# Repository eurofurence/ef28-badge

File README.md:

# Eurofurence 28 Cyber Badge

The cyber LED-Badge is a unique piece of wearable tech. At its core is a rigid
PCB (printed circuit board), assembled with electronic components, carefully
designed to be both functional and visually striking. On the back, you’ll find
a battery pack that powers the badge, ensuring that it can light up in a
spectrum of vibrant colors throughout the event.

The badge features 17 RGB LEDs, which can be controlled to display different
colors and patterns, allowing you to customize your experience. Whether you
want to flash your favorite colors, sync up with others, or simply let your
badge pulse with light as you move through the convention, the choice is yours.

## Technical Details

You can find the full schematics and PCB files in the
[Hardware Details](#hardware-details) section.

- Height: 15.9 cm
- Width: 7.7 cm
- Weight (w/o batteries): 56 g
- Weight (with batteries): ~126 g
- LEDs: 17x WS2812B RGB LEDs
- CPU: ESP32-S3-WROOM-1-N16R8 (Dual-Core, 16MB of Flash, Bluetooth, Wi-Fi)
- Battery holder: 3x AA batteries
- Runtime: Depending on the operation mode and used features, several to many hours
- Unpopulated headers: 2x8 GPIO, SAO 1.69
- User input: 2 touch buttons
- Attachment: Dual-nylon-loop lanyard (included)
- Connectivity: USB-C connector for powering or programming
- Power: Mechanical power switch

# Usage and features

See this page: [How to use your badge](https://www.eurofurence.org/EF28/badge/manual)

## Serial Output / Logging

The badge logs most of its actions and current state onto the serial USB
console. It is available after connecting the badge via USB to your computer
and uses 115200 Baud 8N1.

To read the serial output you can use the serial monitor of your choice, for
example, the integrated serial monitor within VS Code (`CTRL + ALT + S`):

You can also use your favorite serial monitor, for example [minicom](https://salsa.debian.org/minicom-team/minicom):
`minicom -D /dev/ttyACM0 -b 115200`

## Note on LED brightness

You can configure the brightness of your badge, see the manual [How to use your badge](https://www.eurofurence.org/EF28/badge/manual). If you modify your firmware, do not push the LEDs too hard. We limited the brightness on purpose to around 45 of 255 since the 5V boot converter cannot handle more. If you use just one color channel, values up to 100/255 might work. But they are plenty bright at 45 of 255. Higher values cause the 5V rail to break down and the LEDs start flickering badly.

# Building Your Own Firmware

The badge firmware is built using [PlatformIO](https://platformio.org/), an
extension for [Visual Studio Code](https://code.visualstudio.com/) that allows
beginners to quickly get hacking.

### Building with Visual Studio Code (VCS)

To set up your development environment, you need to:

1. Install Visual Studio Code and PlatformIO, as described in the official
   [PlatformIO documentation](https://docs.platformio.org/en/latest/integration/ide/vscode.html#installation)
2. Clone this repository to a suitable location (here: `~/git/ef28-badge`)
3. Open the project under `~/git/ef28-badge` using the PlatformIO IDE
4. Copy `include/secrets.h.dist` to `include/secrets.h` and adjust as needed
5. Execute the build by pressing the build button (1) or using the hotkey (`CTRL + ALT + B`)
6. Check that your build was successful (2)

_Note: The first build can take a while since additional tools and libraries
may need to be downloaded_

### Building from CLI

You can archive most things with the `pio` command from PlatformIO.

* Build firmware: `pio run`
* Upload firmware: `pio run --target upload`
* Clean generated files: `pio run --target clean`
* Attach serial monitor: `pio device monitor`

## Component Overview

The core of this firmware is implemented as a tick-based finite state machine
(FSM). Each operation mode is reflected by a corresponding FSM state.
Interrupts, e.g., from touch zones, trigger events which will be processed by
the FSM in the order they occurred during each tick. Every FSM state can define
its own tick rate. Board features, such as LEDs and touch zones, are available
via easy to use high-level APIs (see `lib/`).

A quick overview of the firmware components:

- `main.cpp`: The main entry point for the firmware. Initializes everything and
  ignites the FSM.
- `include/`: C++ headers
- `include/secrets.h(.dist)`: Custom defines for Wi-Fi and OTA
- `lib/EFBoard/`: Low-level initialization and power management
- `lib/EFLed/`: High-level interface to board LEDs, uses
  [FastLED](https://fastled.io/) under the hood
- `lib/EFLogging/`: Basic serial logging facilities
- `lib/EFTouch/`: High-level interface to touch sensors
- `src/FSM.cpp`: Implementation of the FSM logic
- `src/states/`: Implementation of all FSM states

## Flashing

After you've built your firmware, you can flash it by either connecting the
badge via USB to your computer, or by using over-the-air (OTA) updates.

_Note: OTA updates are only supported after an initial flash using a USB
connection_

### USB

To flash the firmware via USB, you need to:

1. Have a successful build of your firmware
2. Connect the badge via USB to your computer
3. **Close all serial monitors** that use the badges USB device
4. Click the upload button (1) or use the hotkey (`CTRL + ALT + U`)
5. Wait for the flashing to finish (2). Your badge will reboot after flashing.

_Note: Linux users might need to install the
[PlatformIO udev rules](https://docs.platformio.org/en/stable//core/installation/udev-rules.html)
prior to the first flashing._

#### Notes and Pitfalls

If you encounter issues flashing via USB, try the following:

* Some USB cables or ports are flaky. Try a different USB port or change the
  USB-C -> USB-C cable to a USB-A -> USB-C or vice versa.
* Make sure no program is opening the serial port while you flash. For example
  serial monitors in auto-connect mode.
* If it still fails, bridge the boot-pins when turning on. The badge should
  load into a simple bootloader and wait.

### Over-the-Air Updates (OTA)

If you want to flash the badge using over-the-air updates (OTA), it must be
connected to the same Wi-Fi network as your computer.

To flash a badge using OTA, you need to:

1. Make sure to have the correct Wi-Fi credentials supplied in `include/secrets.h`
2. Determine the badge IP address
    - This can be done by connecting your badge to your computer, opening the
      serial monitor, and letting it connect to your Wi-Fi. After a successful
      connection, the badge will print its IP and MAC addresses to the serial console.
3. Uncomment all `upload_*` entries in your `platformio.ini` and adjust
   `upload_port` to the IP address of your badge.
4. Ensure that the badge is in OTA mode
5. Click the upload button or use the hotkey (`CTRL + ALT + U`)
6. Wait for the flashing to finish. The badge will display the OTA progress
   using the LED bar, and the dragon eye will flash three times after a
   successful OTA update.

# Hardware Details

All hardware details, schematics, and PCB files of the badge are released as
[Open Source Hardware](https://www.oshwa.org/). Feel free to share, use, remix,
and extend them to your likings.

You can find the full [KiCad](https://www.kicad.org/) files inside the
`hardware` directory.

For convenience, here is an exported PDF version of the schematics:

# Releases

The release-versions are based on [CalVer](https://calver.org/), with the pattern `vYYYY.MM.DD(-SUB)` where `SUB` is for potential sub-daily releases.

# Useful links

* ESP32-S3 Pin-out and functions: https://github.com/atomic14/esp32-s3-pinouts

# Credits

This badge was designed, crafted and programmed with much love and dedication
by: [DarkRat](https://github.com/dunkelratte), [Token](https://github.com/TokenRat),
[Irah](https://github.com/tridekdu), [Honigeintopf](https://github.com/ngandrass).

The wonderful artwork is done by [Fleeks](https://www.furaffinity.net/user/fleeks).

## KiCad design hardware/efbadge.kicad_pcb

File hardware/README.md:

# Hardware

This is a [KiCad](https://www.kicad.org/) project.

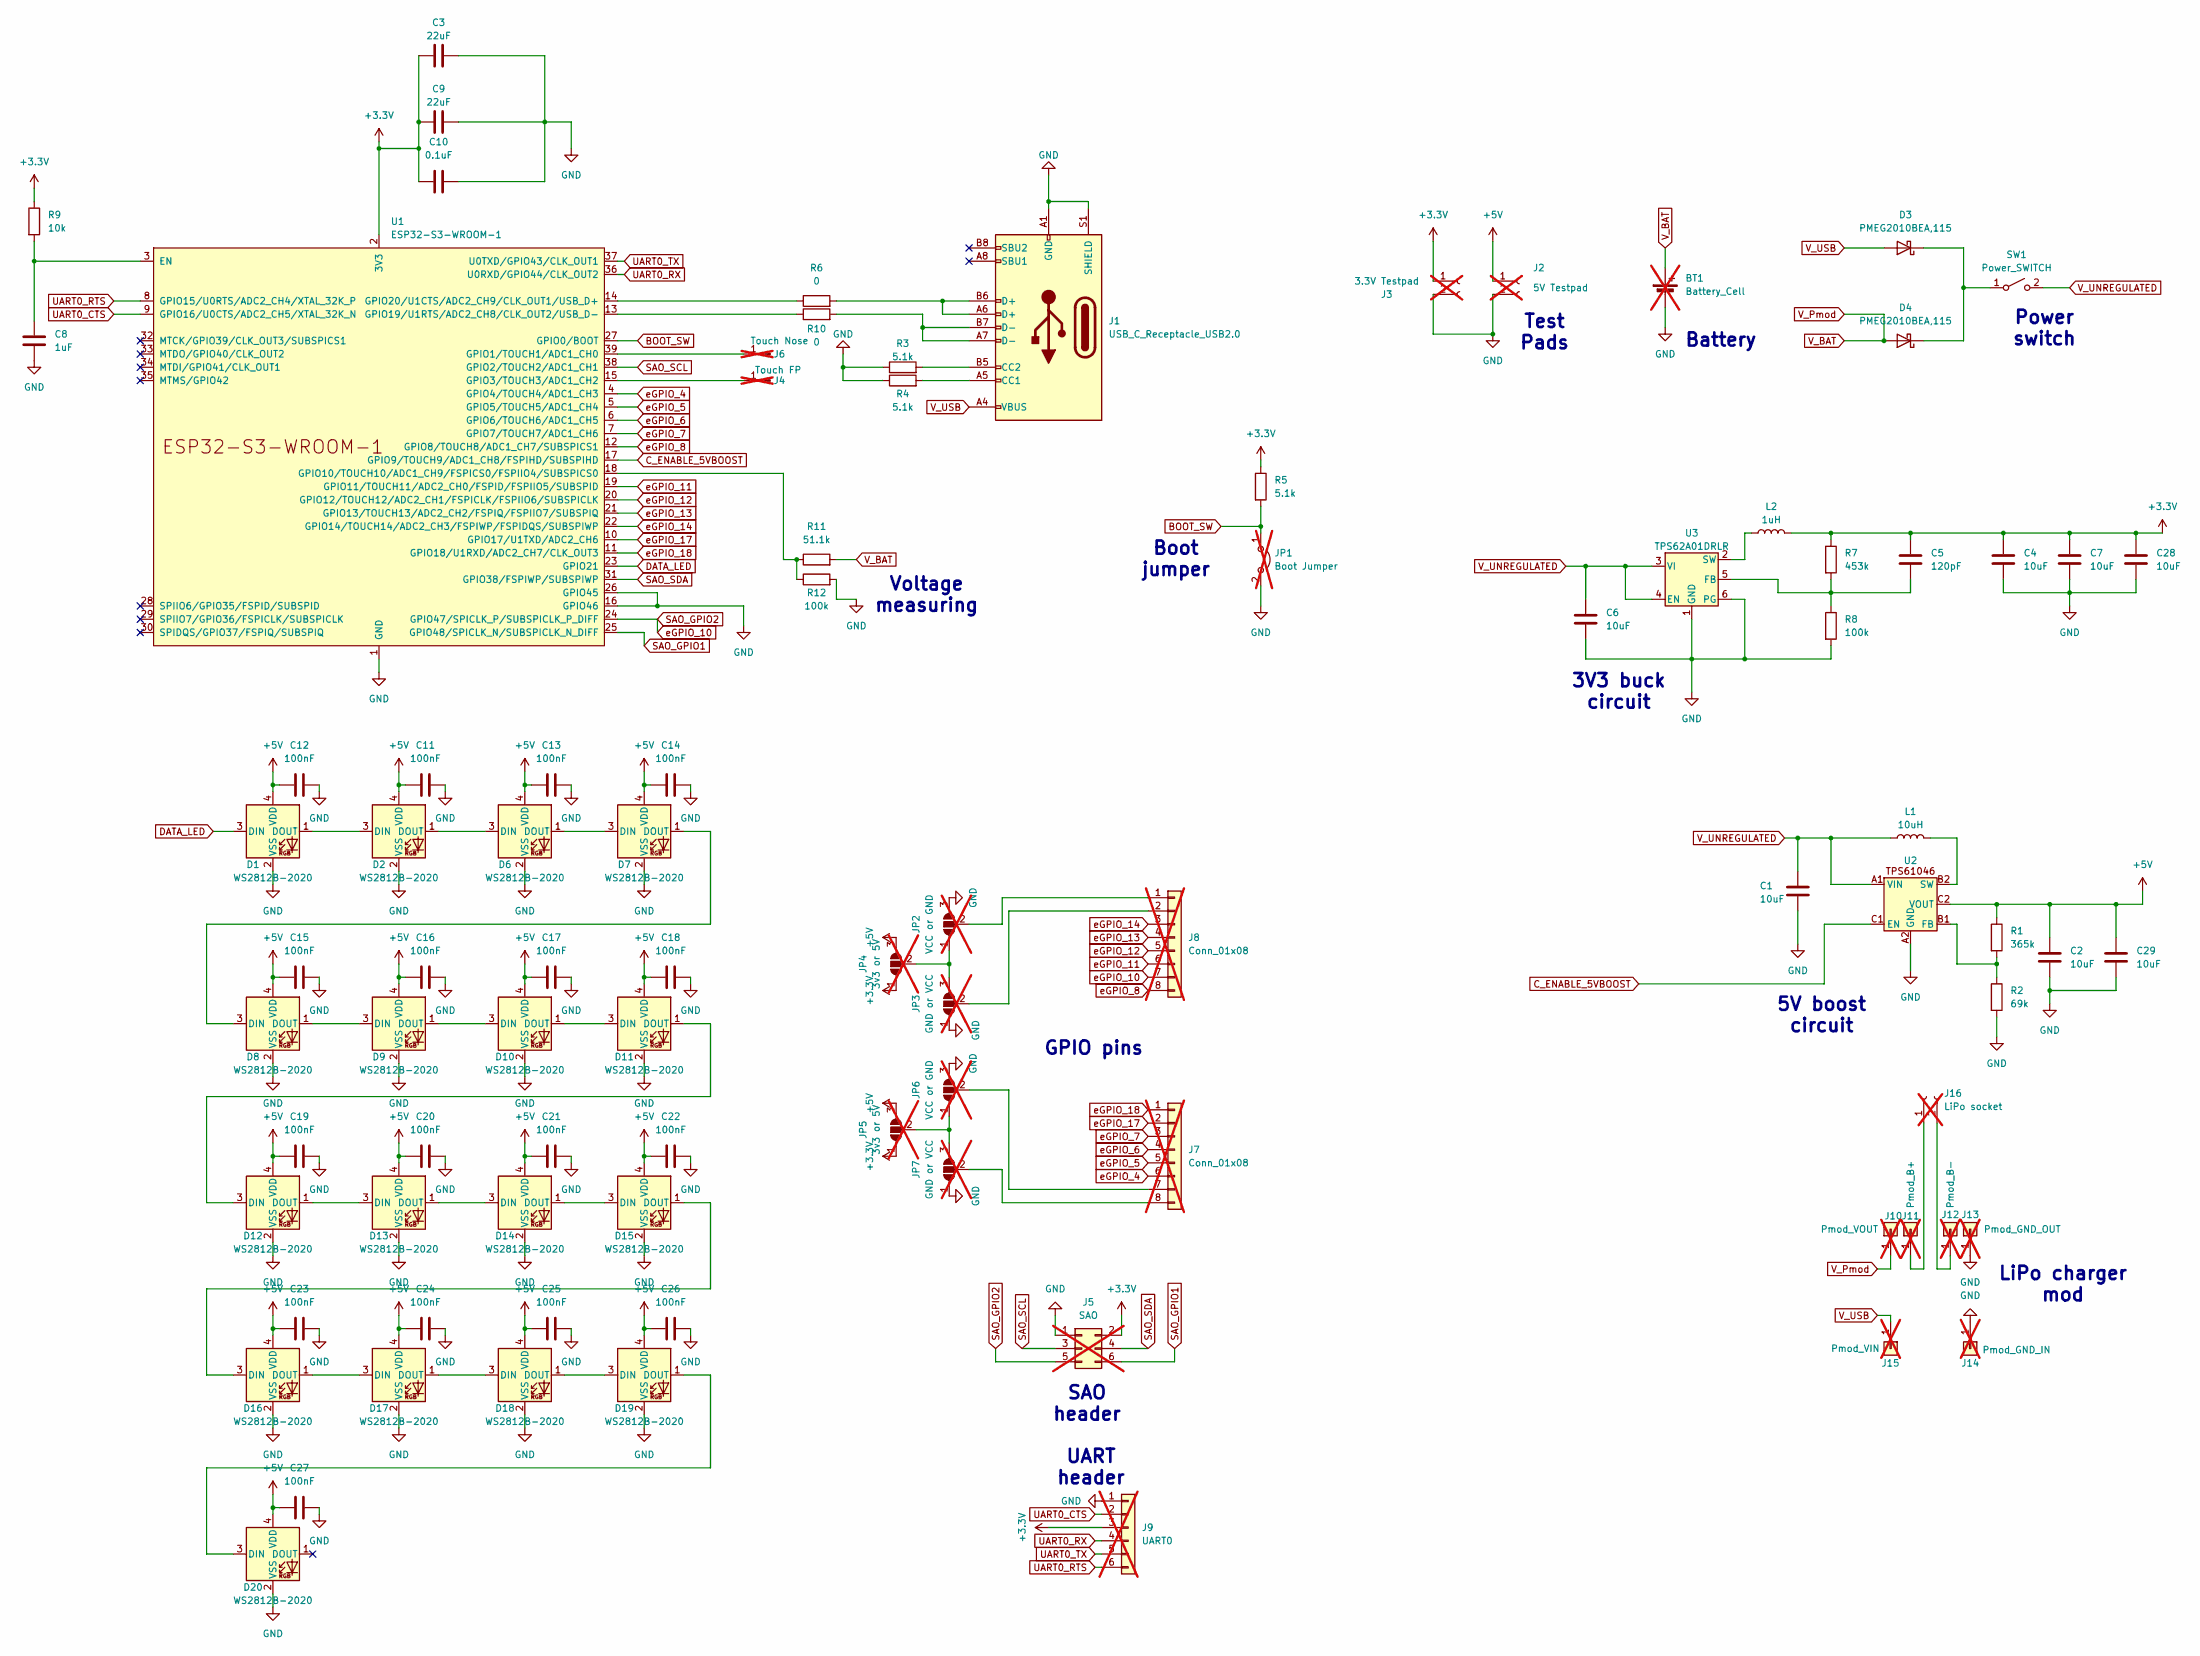
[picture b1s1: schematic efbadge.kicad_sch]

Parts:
BT1: Battery_Cell; BatteryHolder_TruPower_BH-331P_3xAA; Digikey 36-2464-ND; not fitted
C1, C2, C4, C6, C7, C28, C29: 10uF; C_0603_1608Metric; LCSC C182375
C3, C9: 22uF; C_0603_1608Metric; LCSC C15500
C5: 120pF; C_0603_1608Metric; LCSC C61636
C8: 1uF; C_0603_1608Metric; LCSC C309479
C10: 0.1uF; C_0603_1608Metric; LCSC C2846678
C11, C12, C13, C14, C15, C16, C17, C18, C19, C20, C21, C22, C23, C24, C25, C26, C27: 100nF; C_0603_1608Metric_Pad1.08x0.95mm_HandSolder; LCSC C14663
D1, D2, D6, D7, D8, D9, D10, D11, D12, D13, D14, D15, D16, D17, D18, D19, D20: WS2812B-2020; LED_WS2812B-2020_PLCC4_2.0x2.0mm; LCSC C965555
D3, D4: PMEG2010BEA,115; D_SOD-323; LCSC C455041
J1: USB_C_Receptacle_USB2.0; USB_C_Receptacle_G-Switch_GT-USB-7010ASV; LCSC C165948
J2: 5V Testpad; PinHeader_1x02_P2.54mm_Vertical; not fitted
J3: 3.3V Testpad; PinHeader_1x02_P2.54mm_Vertical; not fitted
J4: Touch FP; Badge_Touch; not fitted
J5: SAO; PinHeader_2x03_P2.54mm_Vertical; not fitted
J6: Touch Nose; Badge_Touch; not fitted
J7, J8: Conn_01x08; PinHeader_1x08_P2.54mm_Horizontal; not fitted
J9: UART0; PinHeader_1x06_P2.54mm_Vertical; not fitted
J10: Pmod_VOUT; PinHeader_1x01_P2.54mm_Vertical; not fitted
J11: Pmod_B+; PinHeader_1x01_P2.54mm_Vertical; not fitted
J12: Pmod_B-; PinHeader_1x01_P2.54mm_Vertical; not fitted
J13: Pmod_GND_OUT; PinHeader_1x01_P2.54mm_Vertical; not fitted
J14: Pmod_GND_IN; PinHeader_1x01_P2.54mm_Vertical; not fitted
J15: Pmod_VIN; PinHeader_1x01_P2.54mm_Vertical; not fitted
J16: LiPo socket; JST_PH_S2B-PH-K_1x02_P2.00mm_Horizontal; not fitted
JP1: Boot Jumper; PinHeader_2x01_P2.54mm_Vertical; not fitted
JP2, JP6: VCC or GND; SolderJumper-3_P1.3mm_Open_RoundedPad1.0x1.5mm; not fitted
JP3, JP7: GND or VCC; SolderJumper-3_P1.3mm_Open_RoundedPad1.0x1.5mm; not fitted
JP4, JP5: 3v3 or 5V; SolderJumper-3_P1.3mm_Open_RoundedPad1.0x1.5mm; not fitted
L1: 10uH; L_1008_2520Metric; LCSC C701155
L2: 1uH; L_1008_2520Metric; LCSC C435392
R1: 365k; R_0402_1005Metric; LCSC C3016042
R2: 69k; R_0805_2012Metric; LCSC C2684588
R3, R4, R5: 5.1k; R_1210_3225Metric; LCSC C830191
R6, R10: 0; R_0805_2012Metric; LCSC C844811
R7: 453k; R_0603_1608Metric; LCSC C861412
R8, R12: 100k; R_0603_1608Metric; LCSC C227434
R9: 10k; R_0603_1608Metric; LCSC C209220
R11: 51.1k; R_0402_1005Metric; LCSC C100466
SW1: Power_SWITCH; SW_SPDT_PCM12; LCSC C128955
U1: ESP32-S3-WROOM-1; LCSC C2913201
U2: Texas_DSBGA-6_0.855x1.255mm_Layout2x3_P0.4mm_LevelC; LCSC C181551
U3: TPS62A01DRLR; SOT-563; LCSC C5157937

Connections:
+3.3V: C3.1, C4.1, C5.1, C7.1, C9.1, C10.1, C28.1, J3.1, J5.2, J9.3, JP4.1 (A), JP5.1 (A), L2.2, R5.1, R7.1, R9.1, U1.2 (3V3)
+5V: C2.1, C11.2, C12.2, C13.2, C14.2, C15.2, C16.2, C17.2, C18.2, C19.2, C20.2, C21.2, C22.2, C23.2, C24.2, C25.2, C26.2, C27.2, C29.1, D1.4 (VDD), D2.4 (VDD), D6.4 (VDD), D7.4 (VDD), D8.4 (VDD), D9.4 (VDD), D10.4 (VDD), D11.4 (VDD), D12.4 (VDD), D13.4 (VDD), D14.4 (VDD), D15.4 (VDD), D16.4 (VDD), D17.4 (VDD), D18.4 (VDD), D19.4 (VDD), D20.4 (VDD), J2.1, JP4.3 (B), JP5.3 (B), R1.1, U2.C2 (VOUT)
BOOT_SW: JP1.1 (A), R5.2, U1.27 (GPIO0/BOOT)
C_ENABLE_5VBOOST: U1.17 (GPIO9/TOUCH9/ADC1_CH8/FSPIHD/SUBSPIHD), U2.C1 (EN)
DATA_LED: D1.3 (DIN), U1.23 (GPIO21)
GND: BT1.2 (-), C1.2, C2.2, C3.2, C4.2, C6.2, C7.2, C8.2, C9.2, C10.2, C11.1, C12.1, C13.1, C14.1, C15.1, C16.1, C17.1, C18.1, C19.1, C20.1, C21.1, C22.1, C23.1, C24.1, C25.1, C26.1, C27.1, C28.2, C29.2, D1.2 (VSS), D2.2 (VSS), D6.2 (VSS), D7.2 (VSS), D8.2 (VSS), D9.2 (VSS), D10.2 (VSS), D11.2 (VSS), D12.2 (VSS), D13.2 (VSS), D14.2 (VSS), D15.2 (VSS), D16.2 (VSS), D17.2 (VSS), D18.2 (VSS), D19.2 (VSS), D20.2 (VSS), J1.A1 (GND), J1.A12 (GND), J1.B1 (GND), J1.B12 (GND), J1.S1 (SHIELD), J2.2, J3.2, J5.1, J9.1, J13.1, J14.1, JP1.2 (B), JP2.3 (B), JP3.1 (A), JP6.3 (B), JP7.1 (A), R2.2, R3.1, R4.1, R8.2, R12.2, U1.1 (GND), U1.16 (GPIO46), U1.26 (GPIO45), U1.40 (GND), U1.41 (GND), U2.A2 (GND), U3.1 (GND), U3.6 (PG)
unnamed: D1.1 (DOUT), D2.3 (DIN)
unnamed: D2.1 (DOUT), D6.3 (DIN)
unnamed: D3.1 (K), D4.1 (K), SW1.1 (A)
unnamed: D6.1 (DOUT), D7.3 (DIN)
unnamed: D7.1 (DOUT), D8.3 (DIN)
unnamed: D8.1 (DOUT), D9.3 (DIN)
unnamed: D9.1 (DOUT), D10.3 (DIN)
unnamed: D10.1 (DOUT), D11.3 (DIN)
unnamed: D11.1 (DOUT), D12.3 (DIN)
unnamed: D12.1 (DOUT), D13.3 (DIN)
unnamed: D13.1 (DOUT), D14.3 (DIN)
unnamed: D14.1 (DOUT), D15.3 (DIN)
unnamed: D15.1 (DOUT), D16.3 (DIN)
unnamed: D16.1 (DOUT), D17.3 (DIN)
unnamed: D17.1 (DOUT), D18.3 (DIN)
unnamed: D18.1 (DOUT), D19.3 (DIN)
unnamed: D19.1 (DOUT), D20.3 (DIN)
unnamed: J1.A5 (CC1), R4.2
unnamed: J1.B5 (CC2), R3.2
unnamed: J1.A6 (D+), J1.B6 (D+), R6.2
unnamed: J1.A7 (D-), J1.B7 (D-), R10.2
unnamed: J4.1, U1.15 (GPIO3/TOUCH3/ADC1_CH2)
unnamed: J6.1, U1.39 (GPIO1/TOUCH1/ADC1_CH0)
unnamed: J7.7, JP6.2 (C)
unnamed: J7.8, JP7.2 (C)
unnamed: J8.1, JP2.2 (C)
unnamed: J8.2, JP3.2 (C)
unnamed: J11.1, J16.1
unnamed: J12.1, J16.2
unnamed: JP2.1 (A), JP3.3 (B), JP4.2 (C)
unnamed: JP5.2 (C), JP6.1 (A), JP7.3 (B)
unnamed: C8.1, R9.2, U1.3 (EN)
unnamed: R11.1, R12.1, U1.18 (GPIO10/TOUCH10/ADC1_CH9/FSPICS0/FSPIIO4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)
unnamed: R10.1, U1.13 (GPIO19/U1RTS/ADC2_CH8/CLK_OUT2/USB_D-)
unnamed: R6.1, U1.14 (GPIO20/U1CTS/ADC2_CH9/CLK_OUT1/USB_D+)
unnamed: R1.2, R2.1, U2.B1 (FB)
unnamed: L1.2, U2.B2 (SW)
unnamed: C5.2, R7.2, R8.1, U3.5 (FB)
unnamed: L2.1, U3.2 (SW)
SAO_GPIO1: J5.6, U1.25 (GPIO48/SPICLK_N/SUBSPICLK_N_DIFF)
SAO_GPIO2: J5.5, J8.7, U1.24 (GPIO47/SPICLK_P/SUBSPICLK_P_DIFF)
SAO_SCL: J5.3, U1.38 (GPIO2/TOUCH2/ADC1_CH1)
SAO_SDA: J5.4, U1.31 (GPIO38/FSPIWP/SUBSPIWP)
UART0_CTS: J9.2, U1.9 (GPIO16/U0CTS/ADC2_CH5/XTAL_32K_N)
UART0_RTS: J9.6, U1.8 (GPIO15/U0RTS/ADC2_CH4/XTAL_32K_P)
UART0_RX: J9.4, U1.36 (U0RXD/GPIO44/CLK_OUT2)
UART0_TX: J9.5, U1.37 (U0TXD/GPIO43/CLK_OUT1)
V_BAT: BT1.1 (+), D4.2 (A), J10.1, R11.2
V_UNREGULATED: C1.1, C6.1, L1.1, SW1.2 (B), U2.A1 (VIN), U3.3 (VI), U3.4 (EN)
V_USB: D3.2 (A), J1.A4 (VBUS), J1.A9 (VBUS), J1.B4 (VBUS), J1.B9 (VBUS), J15.1
eGPIO_4: J7.6, U1.4 (GPIO4/TOUCH4/ADC1_CH3)
eGPIO_5: J7.5, U1.5 (GPIO5/TOUCH5/ADC1_CH4)
eGPIO_6: J7.4, U1.6 (GPIO6/TOUCH6/ADC1_CH5)
eGPIO_7: J7.3, U1.7 (GPIO7/TOUCH7/ADC1_CH6)
eGPIO_8: J8.8, U1.12 (GPIO8/TOUCH8/ADC1_CH7/SUBSPICS1)
eGPIO_11: J8.6, U1.19 (GPIO11/TOUCH11/ADC2_CH0/FSPID/FSPIIO5/S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)
eGPIO_12: J8.5, U1.20 (GPIO12/TOUCH12/ADC2_CH1/FSPICLK/FSPIIO6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)
eGPIO_13: J8.4, U1.21 (GPIO13/TOUCH13/ADC2_CH2/FSPIQ/FSPIIO7/S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)
eGPIO_14: J8.3, U1.22 (GPIO14/TOUCH14/ADC2_CH3/FSPIWP/FSPIDQS/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)
eGPIO_17: J7.2, U1.10 (GPIO17/U1TXD/ADC2_CH6)
eGPIO_18: J7.1, U1.11 (GPIO18/U1RXD/ADC2_CH7/CLK_OUT3)

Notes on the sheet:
GPIO pins
LiPo charger mod
Boot jumper
3V3 buck circuit
5V boost circuit
Voltage measuring
UART header
Battery
SAO header
Power switch
Test Pads

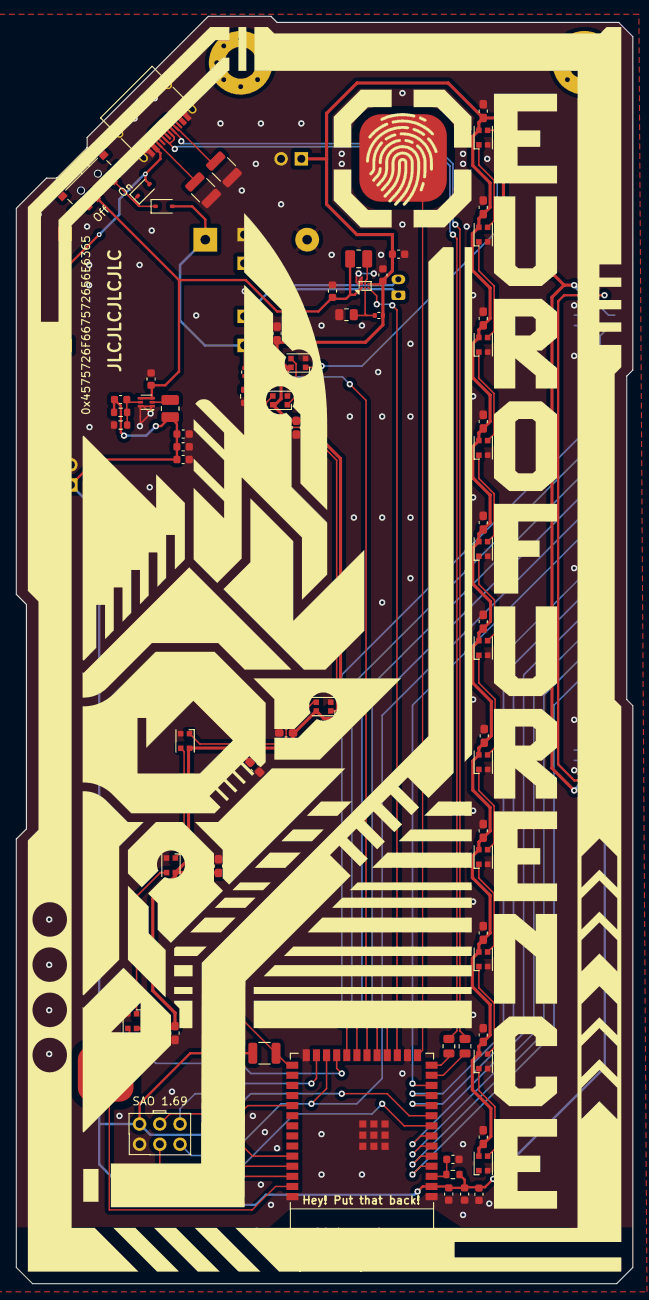
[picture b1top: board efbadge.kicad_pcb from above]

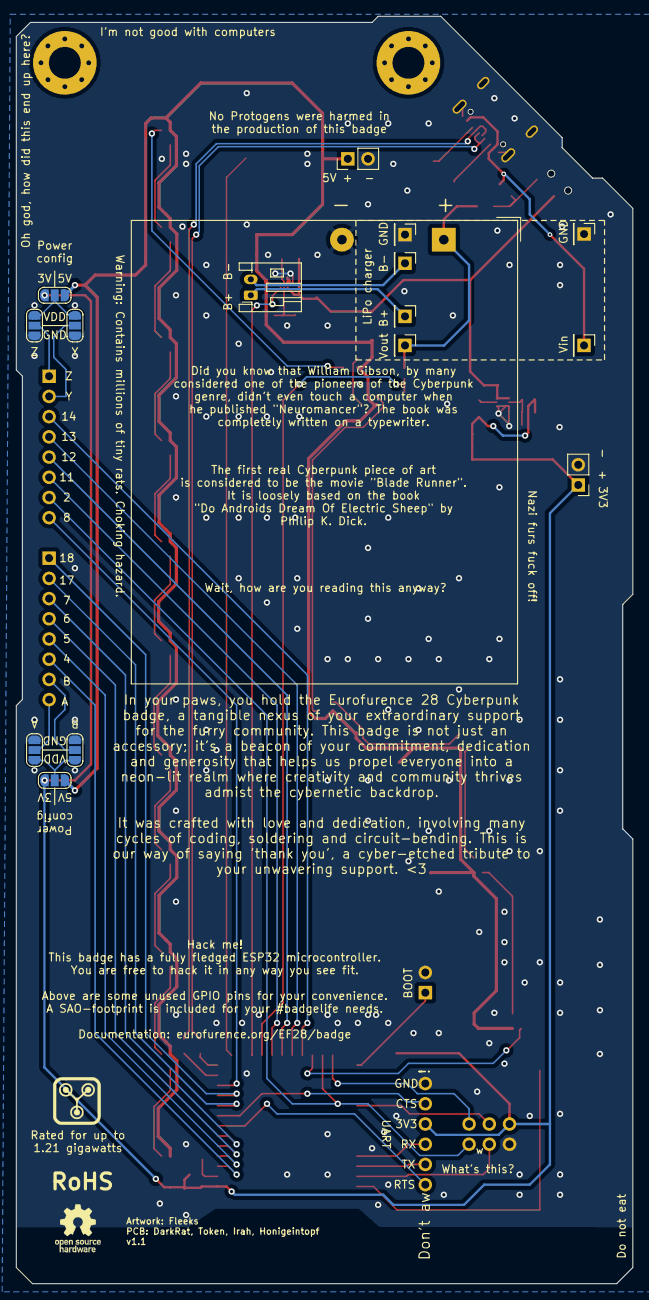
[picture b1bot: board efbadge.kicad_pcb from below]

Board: 2 copper layers, 77.5 x 159.3 mm, 93 parts (16 on the bottom side), 67 nets.

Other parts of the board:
Hole1, Hole2: MountingHole_4mm_Pad_Via
Ref**: Val**; fluxcondensator

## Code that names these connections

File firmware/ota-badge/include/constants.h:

#pragma once

// Pins on EF R0 v0.2 badge
#define PIN_USB_MINUS 19
#define PIN_USB_PLUS 20
#define PIN_TOUCH_NOSE 1
#define PIN_TOUCH_FP 3
#define PIN_EGPIO_4 4
#define PIN_EGPIO_5 5
#define PIN_EGPIO_6 6
#define PIN_EGPIO_7 7
#define PIN_EGPIO_8 8
#define PIN_EGPIO_11 11
#define PIN_EGPIO_12 12
#define PIN_EGPIO_13 13
#define PIN_EGPIO_14 14
#define PIN_EGPIO_17 17
#define PIN_EGPIO_18 18
#define PIN_UART0_RTS 15
#define PIN_UART0_CTS 16
#define PIN_UART0_TX 43
#define PIN_UART0_RX 44
#define PIN_VBAT 10
#define PIN_ENABLE_5VBOOST 9
#define PIN_LED_DATA 21
//#define PIN_ 35
//#define PIN_ 36
//#define PIN_ 37
#define PIN_SAO_SCL 2
#define PIN_SAO_SDA 38
#define PIN_SAO_GPIO_1 48
#define PIN_SAO_GPIO_2 47
//#define PIN_ 39
//#define PIN_ 40
//#define PIN_ 41
//#define PIN_ 42
//#define PIN_ 45 // GND
//#define PIN_ 46 // GND

// LED config
#define LED_TOTAL_NUM 17
#define LED_DRAGON_OFFSET 0
#define LED_DRAGON_NUM 6
#define LED_EF_OFFSET 6
#define LED_EF_NUM 11
#define LED_WIFI_STATUS_IDX 0
#define LED_OTA_STATUS_IDX 1
#define LED_BREATHE_IDX 2
#define LED_EAR_UPPER_IDX 5

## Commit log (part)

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2024-08-22 Create example OTA test firmware
2024-08-22 Update ota-badge firmware
2024-08-22 ota-badge: Create basic pride flag definitions
2024-08-22 Create some easy to use LED wrapper with safety guards for maximum LED brightness
2024-08-22 ota-badge: Force ESP f_cpu to 80MHz via platform config to prevent core booting at 240MHz
2024-08-22 ota-badge: Add serial credits
2024-08-22 ota-badge: Improve OTA visuals and allow for visual debugging using on-board LEDs
2024-08-22 ota-badge: Move hardware initialization, wifi, and OTA code to EFBoard lib
2024-08-22 Refactor ota-badge libs to use Arduino "singleton" pattern
2024-08-22 ota-firmware: Add MIT license to libs
2024-08-22 ota-badge: Improve OTA and setup logging
2024-08-22 ota-badge: Add method to set EFLed bar based on a percentage
2024-08-22 ota-badge: Log firmware version and compilation time during boot
2024-08-22 ota-badge: Add touch zone based ISR support (touched, released, shortpress, longpress) to EFTouch lib
2024-08-22 ota-badge: Add support for log message appending to EFLogging
2024-08-22 Add proper logging facilities
2024-08-22 ota-badge: Move FASTLED config defines to EFLed lib
2024-08-22 ota-badge: Add system time to logs and align everything for improved readability
2024-08-22 ota-badge: Extract EFTouchZone enum class into separate class
2024-08-22 ota-badge: Implement finite state machine that reacts to touch interrupts. Create basic menu structure and allow to enter/exit OTA mode on-demand.
2024-08-22 ota-badge: Remove unused old header file for constants
2024-08-22 ota-badge: Update FastLED to v3.7.3
2024-08-22 ota-badge: Initialize ADC and battery voltage sense pin during board setup
2024-08-22 ota-badge: Create task to periodically log battery voltage / charge when battery is detected
2024-08-22 ota-badge: Remove duplicate files
2024-08-22 ota-badge: Create util functions for enum class to string conversion
2024-08-22 ota-badge: Add methods to EFLed to set all LEDs based on a full color array and to set all LEDs to a single color
2024-08-22 ota-badge: Create functions to measure battery voltage and approximate battery capacity using a discharge function
2024-08-22 ota-badge: Introduce global FSM state to store persistent data between transitions
2024-08-22 ota-badge: Implement board power state management and brown out handling (soft + hard)
2024-08-22 ota-badge: Fully implement pride flag selection menu
2024-08-22 ota-badge: Improve touch interrupt handling. Only trigger one of: Release, Shortpress, Longpress per iteration
2024-08-22 ota-badge: Create animation display / cycle mode
2024-08-22 Make pride flag dragon animations fade smoothely
2024-08-22 Fill empty dragon LEDs during PrideFlag operation mode with cycling flag colors
2024-08-22 Add circular rainbow animation
2024-08-22 Shorten longpress touch duration to 2500 ms
2024-08-22 Give the single tailed rat some neo vibes
2024-08-22 Move firmware folder to repository root
2024-08-23 Cleanup platformio project
2024-08-23 Add license to repository
2024-08-23 Create first WiP draft of README file
2024-08-26 Ignore KiCad temp files
2024-08-26 Add KiCad project files (schematic, PCB, ...)
2024-08-26 Make schematic fit page area
2024-08-26 Create PDF and PNG exports of the badge schematics
2024-08-26 Add hardware details section to README and link PDF export
2024-08-27 Create note about availability of KiCad project files inside hardware directory
2024-08-27 Graphic amended.
2024-08-28 feat: Add .editorconfig
    Sets some common whitespace settings for VSCode, Idea and some other IDEs. Helps to keep contributions will less whitespace conflicts.
2024-08-28 Typo fixes
2024-08-28 Add GitHub workflows
    This adds a test-workflow that tests compiling
2024-08-28 Add issue templates
    This auto-adds tags
2024-08-28 Add comment
2024-08-28 Configure renovate
2024-08-28 Fix test action
2024-08-28 Typo fix
2024-08-28 Add release GitHub workflow
    Still needs documentation and does not work like this yet
2024-08-28 Add some PlatformIO help
2024-08-31 Typo and documentation clarification
2024-08-31 Update FastLED
2024-08-31 Refine battery values
    In my tests, the ESP runs with the batteries at 3,28. it just fails to start up at below VBAT 3,3V. But if the batteries are given a few seconds to recover, it works. And while it is running, we do g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
2024-08-31 Refactor EFLedClass methods for consistency and clarity
    Some can be static. Others do not modify the state of the lass so could be const. I hope. Not a C++ expert, but my static analyzer told me. :P
    It also told me that const on the definitions do not do anything, but only on the actual methods. So also cleaned that up.
2024-08-31 Tweak power settings
2024-08-31 Typo fix and whitespace cleanup
2024-08-31 Fix pinout on graphics
2024-08-31 Remov const from setBrightness
2024-09-01 Fix whitespace
2024-09-01 Tweak battery values to something slightly more safe
    After some discussion.
2024-09-01 Re-add const to interface
    While my linter says it is not necessary, it does not harm and Honig said we should keep it - so we do. :D
2024-09-01 chore: Cleanups and typos
2024-09-02 Remove blink LED task code as task handler was removed by previous commit but actual implementation code did not get cleaned up
2024-09-02 Persist current FSM globals into NVS if requested by state
2024-09-02 Allow FSM states to declare them self as resumable and persist this info to NVS for resuming the FSM after boot
2024-09-02 Set DisplayPrideFlag with flag 1 (LGBT) as default for first boot
2024-09-02 Convert OTAUpdate state into proper main state, reachable via the MainMenu normal navigation pattern
2024-09-02 Remove sub state settings menu from DisplayPrideFlag and allow switching current flag/pattern by touching fingerprint zone in normal operation state
2024-09-02 Reduce boot delay for upcoming production release
2024-09-02 Separate DisplayAnimation state into: AnimateRainbow, AnimateMatrix, AnimateSnake
2024-09-02 Simplify FSM state resuming and persist at any point in time if globals got dirtied
2024-09-02 Fix typo
2024-09-02 Fix pin mapping in EFTouch constructor
2024-09-03 Introduce constant for battery check
2024-09-03 chore: setBrightness to setBrightnessPercent
    The function takes a value between 0 and 100, this makes it more clear.
2024-09-04 Enable positional animation of LEDs
2024-09-04 Add cppcheck to test-workflow
2024-09-04 Do not check dependencies
2024-09-04 Add heartbeat animation
2024-09-04 Remove unsued import
2024-09-04 Decrease touch-delay limits
    I have been testing around in some modes and only now really realized that a 'Release' event is not a ShortTouch.
    Which is okay that we do it like this. We basically get three modes out of a button: Tap, ShortPress, LongPress.
    But when playing around, it felt very sluggish. I thought the ShortPress mode was broken because it felt like a LongPress. :P
    I researched online on UX studies and what kind of reaction people expect from Touch-UIs. Usually, a touch->interaction latency should be below 300ms. This is the Tap -> Response delay and not necess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
2024-09-05 Add fancy bootup animation
2024-09-05 Update README with credits and flashing hints
    After finding out some flashing quirks, I put them into the readme. Also linked our usernames.
2024-09-05 Remove initial delay
    After tweaking my flashing settings, it now always works. Does it work for you as well? If so, let's remove this annoying delay at the start.
    Also tweaked the FastLED delay in the hope to reduce the flicker of the LEDs, but it is still there. =/
2024-09-05 Hard-wrap long lines in README
2024-09-05 Move flashing notes into flashing section and make headings for building with VCS / CLI clearer
2024-09-05 Fix indentation of AnimateHeartbeat declaration
2024-09-05 Persist AnimateHeartbeat settings to NVS
2024-09-05 Remove superfluous / unimplemented function definition EFBoard::bootupAnimation() (is located in main.cpp)
2024-09-05 Fix OTAUpdate state not reachable via MenuMain
2024-09-05 Add basic docs for new functions
2024-09-06 Tweak a bunch of values
    Sorry for yet another mixed-bag PR, but the more I test around, the better values I find I think.
    The 'longPress' can be verbalized/explained by 'hold the button and count to three' -> this naturally *almost* works. I decreased the delay from 2000ms to 1800ms, then it works nicely like this with 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
2024-09-06 Improve MainMenu, add brightness control
    Somehow it is not yet correctly persisted. I think I am loading globals incorrectly in main.cpp and that makes it reset this to the default value.
2024-09-06 Fix NVS persistence storage of ledBrightnessPercent
2024-09-06 Remove second globals object from main.cpp (real instance is inside FSM class)
2024-09-06 Properly restore global LED brightness setting on FSM resume
2024-09-06 Minor renaming fix
2024-09-06 Add changelog
2024-09-06 feat: add Perlin noise animation
    Introduce new "AnimatePerlin" state to the FSM for displaying Perlin noise patterns. Updated global variables and menu selections to support the new animation mode.
2024-09-06 Fix: Battery voltage reading
    It seems to be off. Trying to make it a bit more robust and the badge go less into soft_brownout_detection if it is not really needed.
2024-09-06 fix: update led brightness handling and delay timings
2024-09-06 Adding more colors to the matrix animation
2024-09-06 Adding .idea to gitignore
2024-09-06 Fix AnimateMatrix not reaching all configured hues
2024-09-06 Extend AnimateMatrix to support some more hues because people like customization <3
2024-09-06 Fix FSMGlobals comments and their indentation
2024-09-06 Improve touch handling
2024-09-06 Add support for detecting multi zone touch events to EFTouch
2024-09-06 Make FSM sensitive to multi zone touch events
2024-09-06 Implement button locking to all main run states
2024-09-06 Fix multitouch race condition when lifting fingers from touch zones
2024-09-06 Adding pulse/scanner animation
2024-09-06 Adding "random" lightup animation
2024-09-06 fix: improve battery voltage calculation accuracy
    The old measurements were off and always cut off a lot of battery runtime from the badges!
2024-09-07 fix: improve low power handling
2024-09-07 feat: add autoflash script for automatic device flashing
    Introduce `autoflash.sh` to continuously monitor a specified device
    port, automatically flash firmware upon device detection, and log
    results. This enhances the flashing process by making it more efficient
    and less manual.
    Yay for two days of continuous preparing and flashing! :D
2024-09-07 Do battery checks in the boopup
2024-09-07 Disabling OTA for production code
2024-09-07 Tweak power value
2024-09-07 Setting a random animation on first bootup
2024-09-08 Tweak autoflash
2024-09-10 Cleanup getBatteryVoltage
2024-09-10 Make out-of-power state a bit more visible
2024-09-10 Remove cruft
2024-09-12 Release v2024.09.07
2024-09-15 Moved "WaveFunction" to utils
2024-09-15 Did game
2024-09-15 Refactor and unfuckify
2024-09-15 Adding a pio script to merge the firmware binaries into a single file
2024-09-17 Replace hardware files publication note with link to KiCad software
2024-09-18 Fix Arial font usage on PCB back silkscreen
2024-09-19 VUMeter patch
2024-09-19 potential float fix
2024-09-19 Add changelog entry
2024-09-19 Update changelog
2024-09-23 Add manual and warning about LED brightness
    Add manual and warning about LED brightness to the README
